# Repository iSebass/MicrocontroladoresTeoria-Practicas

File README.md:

# MicrocontroladoresTeoria-Practicas
Este repositorio ha sido creado como un recurso de apoyo para el curso de Microcontroladores impartido en la Universidad del Valle. En este espacio colaboraremos con el Dr. en Ingeniería Sergio Arenas y el Ing. Juan Sebastián Correa. Nuestro objetivo es desarrollar contenido actualizado que promueva un aprendizaje de los estudiantes.

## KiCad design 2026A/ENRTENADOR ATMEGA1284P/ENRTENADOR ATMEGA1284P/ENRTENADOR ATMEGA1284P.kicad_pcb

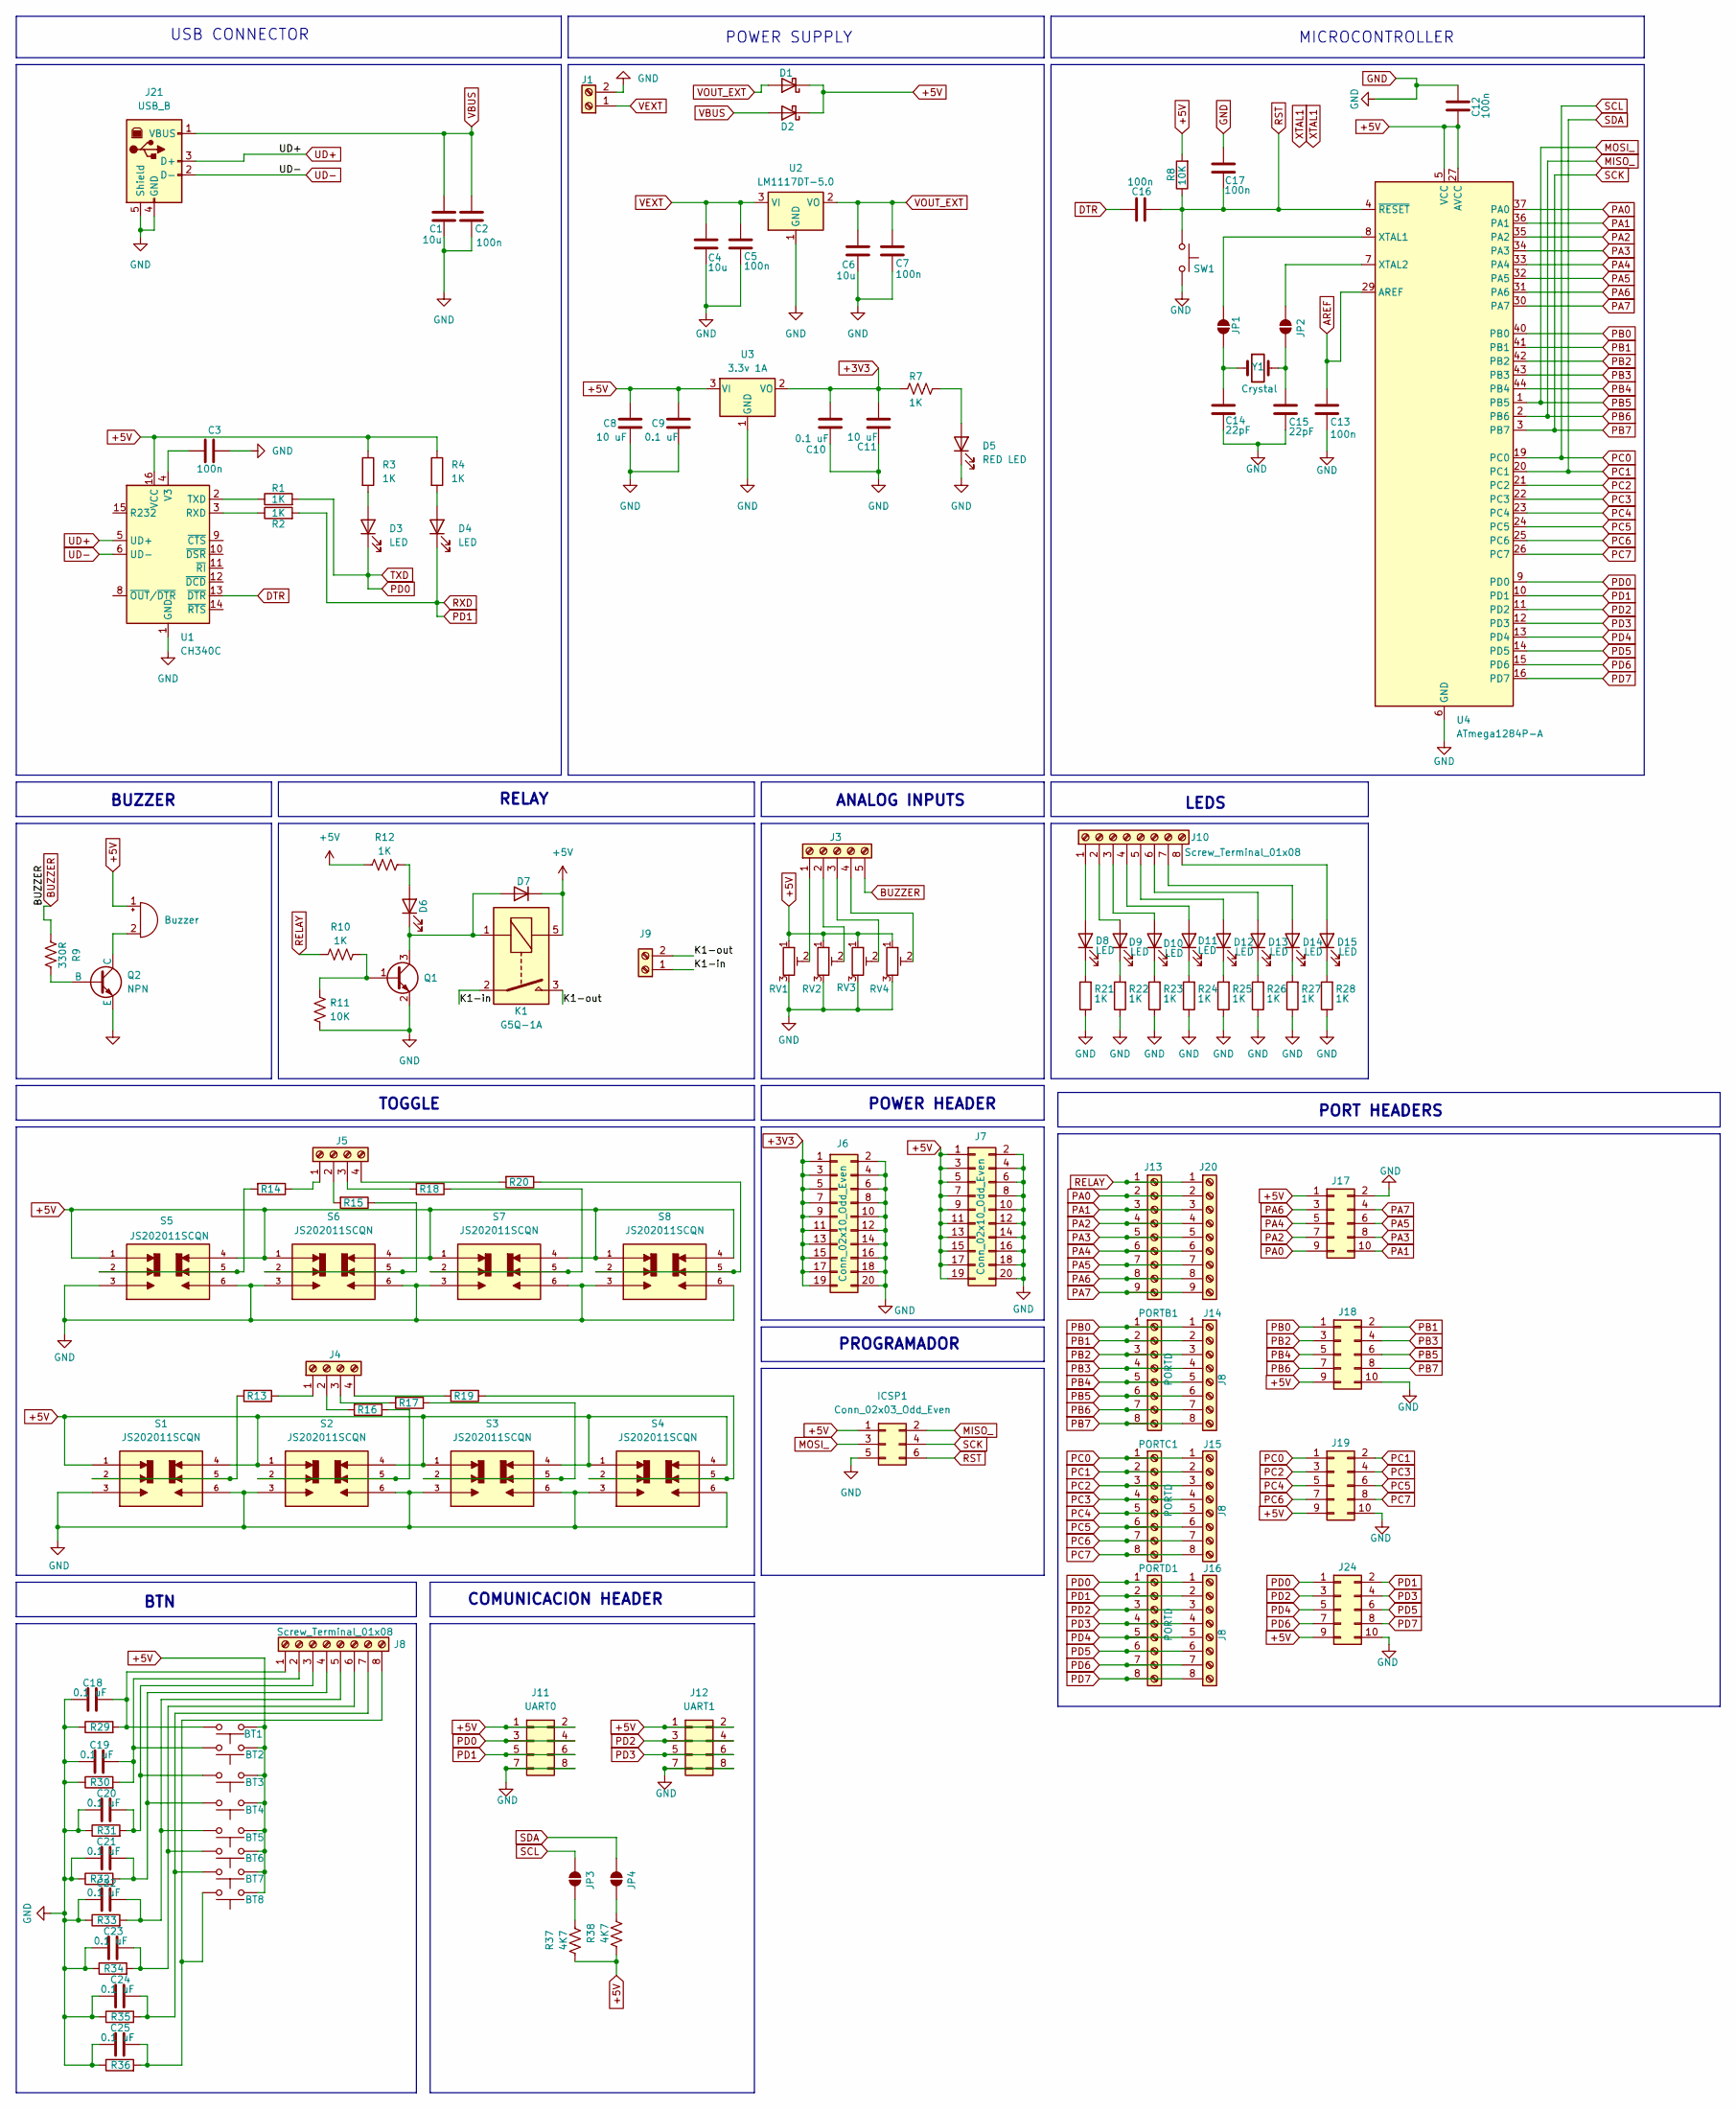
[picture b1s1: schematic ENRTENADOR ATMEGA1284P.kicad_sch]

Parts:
BT1, BT2, BT3, BT4, BT5, BT6, BT7, BT8: SW_Push; SW_SPST_CK_RS282G05A3
BZ1: Buzzer; Buzzer_12x9.5RM7.6
C1, C4, C6: 10u; C_0805_2012Metric
C2, C3, C5, C7, C12, C13, C16, C17: 100n; C_0805_2012Metric
C8, C11: 10 uF; C_0805_2012Metric
C9, C10, C18, C19, C20, C21, C22, C23, C24, C25: 0.1 uF; C_0805_2012Metric
C14, C15: 22pF; C_0805_2012Metric
D1, D2: D_Schottky; D_SMA
D3, D4, D8, D9, D10, D11, D12, D13, D14, D15: LED; LED_0805_2012Metric
D5: RED LED; LED_0805_2012Metric
D6: Green LED; LED_0805_2012Metric
D7: NRVA4007T3G; D_SMA
ICSP1: Conn_02x03_Odd_Even; PinHeader_2x03_P2.54mm_Horizontal
J1, J9: Screw_Terminal_01x02; TerminalBlock_Phoenix_MKDS-1,5-2_1x02_P5.00mm_Horizontal
J3: Screw_Terminal_01x05; PinHeader_1x05_P2.54mm_Vertical
J4, J5: Screw_Terminal_01x04; PinHeader_1x04_P2.54mm_Vertical
J6, J7: Conn_02x10_Odd_Even; PinHeader_2x10_P2.54mm_Vertical
J8, J10: Screw_Terminal_01x08; PinHeader_1x08_P2.54mm_Vertical
J11: UART0; PinHeader_2x04_P2.54mm_Vertical
J12: UART1; PinHeader_2x04_P2.54mm_Vertical
J13, J20: Screw_Terminal_01x09; PinHeader_1x09_P2.54mm_Vertical
J14, J15, J16: J8; PinHeader_1x08_P2.54mm_Vertical
J17, J18, J19, J24: Conn_02x05_Odd_Even; IDC-Header_2x05_P2.54mm_Vertical
J21: USB_B; USB_B_OST_USB-B1HSxx_Horizontal
JP1, JP2, JP3, JP4: SolderJumper_2_Open; SolderJumper-2_P1.3mm_Open_RoundedPad1.0x1.5mm
K1: G5Q-1A; Relay_SPST_Omron-G5Q-1A
PORTB1: PORTD; PinHeader_1x08_P2.54mm_Vertical
PORTC1: PORTD; PinHeader_1x08_P2.54mm_Vertical
PORTD1: PORTD; PinHeader_1x08_P2.54mm_Vertical
Q1: Q_NPN_BEC; SOT-23-3
Q2: NPN; TO-92
R1, R2, R3, R4, R7, R10, R12, R21, R22, R23, R24, R25, R26, R27, R28: 1K; R_0805_2012Metric
R8, R11, R13, R14, R15, R16, R17, R18, R19, R20, R29, R30, R31, R32, R33, R34, R35, R36: 10K; R_0805_2012Metric
R9: 330R; R_1206_3216Metric
R37, R38: 4K7; R_1206_3216Metric
RV1, RV2, RV3, RV4: R_Potentiometer_Trim; Potentiometer_Bourns_TC33X_Vertical
S1, S2, S3, S4, S5, S6, S7, S8: JS202011SCQN; SW_JS202011SCQN; PARTREV 26 May 22
SW1: SW_Push; SW_SPST_CK_RS282G05A3
U1: CH340C; SOIC-16_3.9x9.9mm_P1.27mm
U2: LM1117DT-5.0; TO-252-3_TabPin2
U3: 3.3v 1A; SOT-223-3_TabPin2
U4: ATmega1284P-A; TQFP-44_10x10mm_P0.8mm
Y1: Crystal; Crystal_SMD_HC49-SD

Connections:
+3V3: C10.1, C11.1, J6.1, J6.3, J6.5, J6.7, J6.9, J6.11, J6.13, J6.15, J6.17, J6.19, R7.1, U3.2 (VO)
+5V: BT1.1, BT2.1, BT3.1, BT4.1, BT5.1, BT6.1, BT7.1, BT8.1, BZ1.1 (-), C8.1, C9.1, C12.1, D1.1 (K), D2.1 (K), D7.1 (K), ICSP1.1, J7.1, J7.3, J7.5, J7.7, J7.9, J7.11, J7.13, J7.15, J7.17, J7.19, J11.1, J11.2, J12.1, J12.2, J17.1, J18.9, J19.9, J24.9, K1.5, R3.1, R4.1, R8.2, R12.1, R37.1, R38.1, RV1.1, RV2.1, RV3.1, RV4.1, S1.1, S1.4, S2.1, S2.4, S3.1, S3.4, S4.1, S4.4, S5.1, S5.4, S6.1, S6.4, S7.1, S7.4, S8.1, S8.4, U1.16 (VCC), U3.3 (VI), U4.5 (VCC), U4.17 (VCC), U4.27 (AVCC), U4.38 (VCC)
/K1-in: J9.1, K1.2
/K1-out: J9.2, K1.3
AREF: C13.1, U4.29 (AREF)
BUZZER: J3.5, R9.1
DTR: C16.2, U1.13 (~DTR)
GND: C1.2, C2.2, C3.2, C4.2, C5.2, C6.2, C7.2, C8.2, C9.2, C10.2, C11.2, C12.2, C13.2, C14.2, C15.2, C17.2, C18.1, C19.1, C20.1, C21.1, C22.1, C23.1, C24.1, C25.1, D5.1 (K), ICSP1.5, J1.2, J6.2, J6.4, J6.6, J6.8, J6.10, J6.12, J6.14, J6.16, J6.18, J6.20, J7.2, J7.4, J7.6, J7.8, J7.10, J7.12, J7.14, J7.16, J7.18, J7.20, J11.7, J11.8, J12.7, J12.8, J17.2, J18.10, J19.10, J21.4 (GND), J21.5 (Shield), J24.10, Q1.2 (E), Q2.3 (E), R11.1, R21.1, R22.1, R23.1, R24.1, R25.1, R26.1, R27.1, R28.1, R29.1, R30.1, R31.1, R32.1, R33.1, R34.1, R35.1, R36.1, RV1.3, RV2.3, RV3.3, RV4.3, S1.3, S1.6, S2.3, S2.6, S3.3, S3.6, S4.3, S4.6, S5.3, S5.6, S6.3, S6.6, S7.3, S7.6, S8.3, S8.6, SW1.2, U1.1 (GND), U2.1 (GND), U3.1 (GND), U4.6 (GND), U4.18 (GND), U4.28 (GND), U4.39 (GND)
MISO_: ICSP1.2, J14.7, J18.7, PORTB1.7, U4.2 (PB6)
MOSI_: ICSP1.3, J14.6, J18.6, PORTB1.6, U4.1 (PB5)
unnamed: BZ1.2 (+), Q2.1 (C)
unnamed: D3.2 (A), R3.2
unnamed: D4.2 (A), R4.2
unnamed: D5.2 (A), R7.2
unnamed: D6.2 (A), R12.2
unnamed: D6.1 (K), D7.2 (A), K1.1, Q1.3 (C)
unnamed: D8.2 (A), J10.1
unnamed: D8.1 (K), R21.2
unnamed: D9.2 (A), J10.2
unnamed: D9.1 (K), R22.2
unnamed: D10.2 (A), J10.3
unnamed: D10.1 (K), R23.2
unnamed: D11.2 (A), J10.4
unnamed: D11.1 (K), R24.2
unnamed: D12.2 (A), J10.5
unnamed: D12.1 (K), R25.2
unnamed: D13.2 (A), J10.6
unnamed: D13.1 (K), R26.2
unnamed: D14.2 (A), J10.7
unnamed: D14.1 (K), R27.2
unnamed: D15.2 (A), J10.8
unnamed: D15.1 (K), R28.2
unnamed: J3.1, RV1.2
unnamed: J3.2, RV2.2
unnamed: J3.3, RV3.2
unnamed: J3.4, RV4.2
unnamed: J4.1, R13.1
unnamed: J4.2, R16.2
unnamed: J4.3, R17.2
unnamed: J4.4, R19.2
unnamed: J5.1, R14.1
unnamed: J5.2, R15.2
unnamed: J5.3, R18.2
unnamed: J5.4, R20.2
unnamed: BT1.2, C18.2, J8.1, R29.2
unnamed: BT2.2, C19.2, J8.2, R30.2
unnamed: BT3.2, C20.2, J8.3, R31.2
unnamed: BT4.2, C21.2, J8.4, R32.2
unnamed: BT5.2, C22.2, J8.5, R33.2
unnamed: BT6.2, C23.2, J8.6, R34.2
unnamed: BT7.2, C24.2, J8.7, R35.2
unnamed: BT8.2, C25.2, J8.8, R36.2
unnamed: JP1.1 (A), U4.8 (XTAL1)
unnamed: C14.1, JP1.2 (B), Y1.1
unnamed: JP2.1 (A), U4.7 (XTAL2)
unnamed: C15.1, JP2.2 (B), Y1.2
unnamed: JP3.2 (B), R37.2
unnamed: JP4.2 (B), R38.2
unnamed: Q1.1 (B), R10.2, R11.2
unnamed: Q2.2 (B), R9.2
unnamed: R13.2, S1.2, S1.5
unnamed: R14.2, S5.2, S5.5
unnamed: R15.1, S6.2, S6.5
unnamed: R16.1, S2.2, S2.5
unnamed: R17.1, S3.2, S3.5
unnamed: R18.1, S7.2, S7.5
unnamed: R19.1, S4.2, S4.5
unnamed: R20.1, S8.2, S8.5
unnamed: R2.1, U1.3 (RXD)
unnamed: R1.1, U1.2 (TXD)
unnamed: C3.1, U1.4 (V3)
PA0: J13.2, J17.9, J20.2, U4.37 (PA0)
PA1: J13.3, J17.10, J20.3, U4.36 (PA1)
PA2: J13.4, J17.7, J20.4, U4.35 (PA2)
PA3: J13.5, J17.8, J20.5, U4.34 (PA3)
PA4: J13.6, J17.5, J20.6, U4.33 (PA4)
PA5: J13.7, J17.6, J20.7, U4.32 (PA5)
PA6: J13.8, J17.3, J20.8, U4.31 (PA6)
PA7: J13.9, J17.4, J20.9, U4.30 (PA7)
PB0: J14.1, J18.1, PORTB1.1, U4.40 (PB0)
PB1: J14.2, J18.2, PORTB1.2, U4.41 (PB1)
PB2: J14.3, J18.3, PORTB1.3, U4.42 (PB2)
PB3: J14.4, J18.4, PORTB1.4, U4.43 (PB3)
PB4: J14.5, J18.5, PORTB1.5, U4.44 (PB4)
PB7: ICSP1.4, J14.8, J18.8, PORTB1.8, U4.3 (PB7)
PC0: J15.1, J19.1, JP3.1 (A), PORTC1.1, U4.19 (PC0)
PC1: J15.2, J19.2, JP4.1 (A), PORTC1.2, U4.20 (PC1)
PC2: J15.3, J19.3, PORTC1.3, U4.21 (PC2)
PC3: J15.4, J19.4, PORTC1.4, U4.22 (PC3)
PC4: J15.5, J19.5, PORTC1.5, U4.23 (PC4)
PC5: J15.6, J19.6, PORTC1.6, U4.24 (PC5)
PC6: J15.7, J19.7, PORTC1.7, U4.25 (PC6)
PC7: J15.8, J19.8, PORTC1.8, U4.26 (PC7)
PD0: D3.1 (K), J11.3, J11.4, J16.1, J24.1, PORTD1.1, R1.2, U4.9 (PD0)
PD1: D4.1 (K), J11.5, J11.6, J16.2, J24.2, PORTD1.2, R2.2, U4.10 (PD1)
PD2: J12.3, J12.4, J16.3, J24.3, PORTD1.3, U4.11 (PD2)
PD3: J12.5, J12.6, J16.4, J24.4, PORTD1.4, U4.12 (PD3)
PD4: J16.5, J24.5, PORTD1.5, U4.13 (PD4)
PD5: J16.6, J24.6, PORTD1.6, U4.14 (PD5)
PD6: J16.7, J24.7, PORTD1.7, U4.15 (PD6)
PD7: J16.8, J24.8, PORTD1.8, U4.16 (PD7)
RELAY: J13.1, J20.1, R10.1
RST: C16.1, C17.1, ICSP1.6, R8.1, SW1.1, U4.4 (~RESET)
UD+: J21.3 (D+), U1.5 (UD+)
UD-: J21.2 (D-), U1.6 (UD-)
VBUS: C1.1, C2.1, D2.2 (A), J21.1 (VBUS)
VEXT: C4.1, C5.1, J1.1, U2.3 (VI)
VOUT_EXT: C6.1, C7.1, D1.2 (A), U2.2 (VO)

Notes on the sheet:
LEDS
PROGRAMADOR
COMUNICACION HEADER
POWER SUPPLY
BUZZER
ANALOG INPUTS
TOGGLE
BTN
RELAY
PORT HEADERS
MICROCONTROLLER
POWER HEADER
USB CONNECTOR

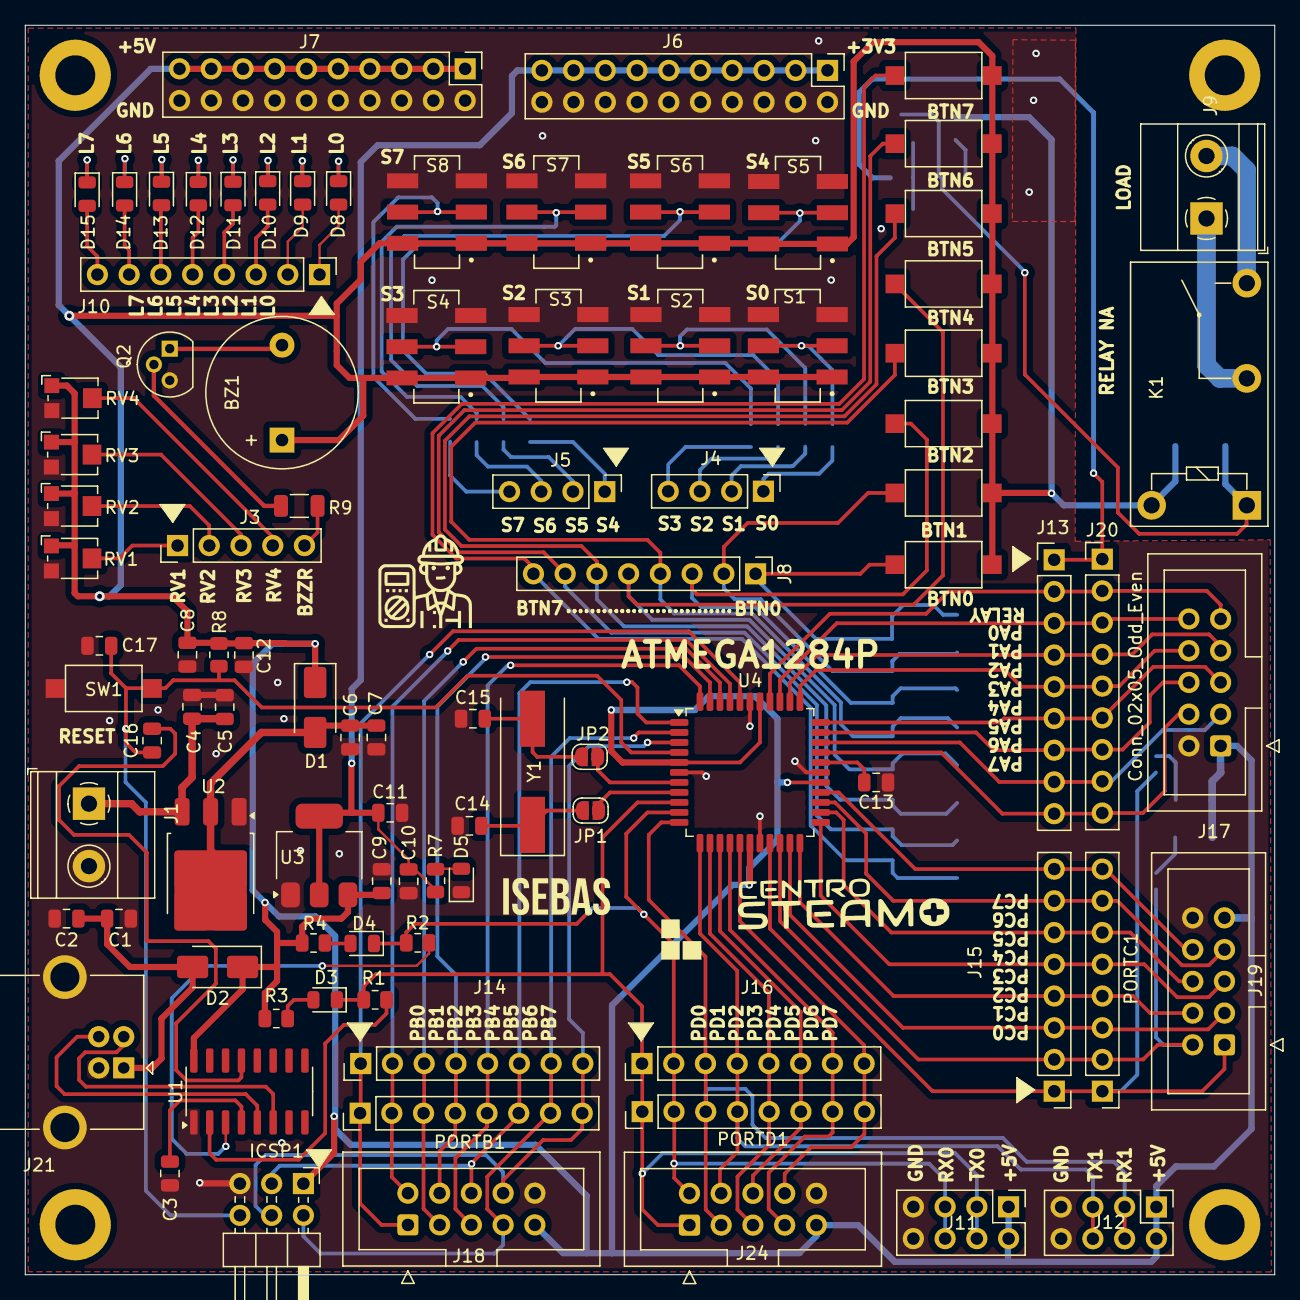
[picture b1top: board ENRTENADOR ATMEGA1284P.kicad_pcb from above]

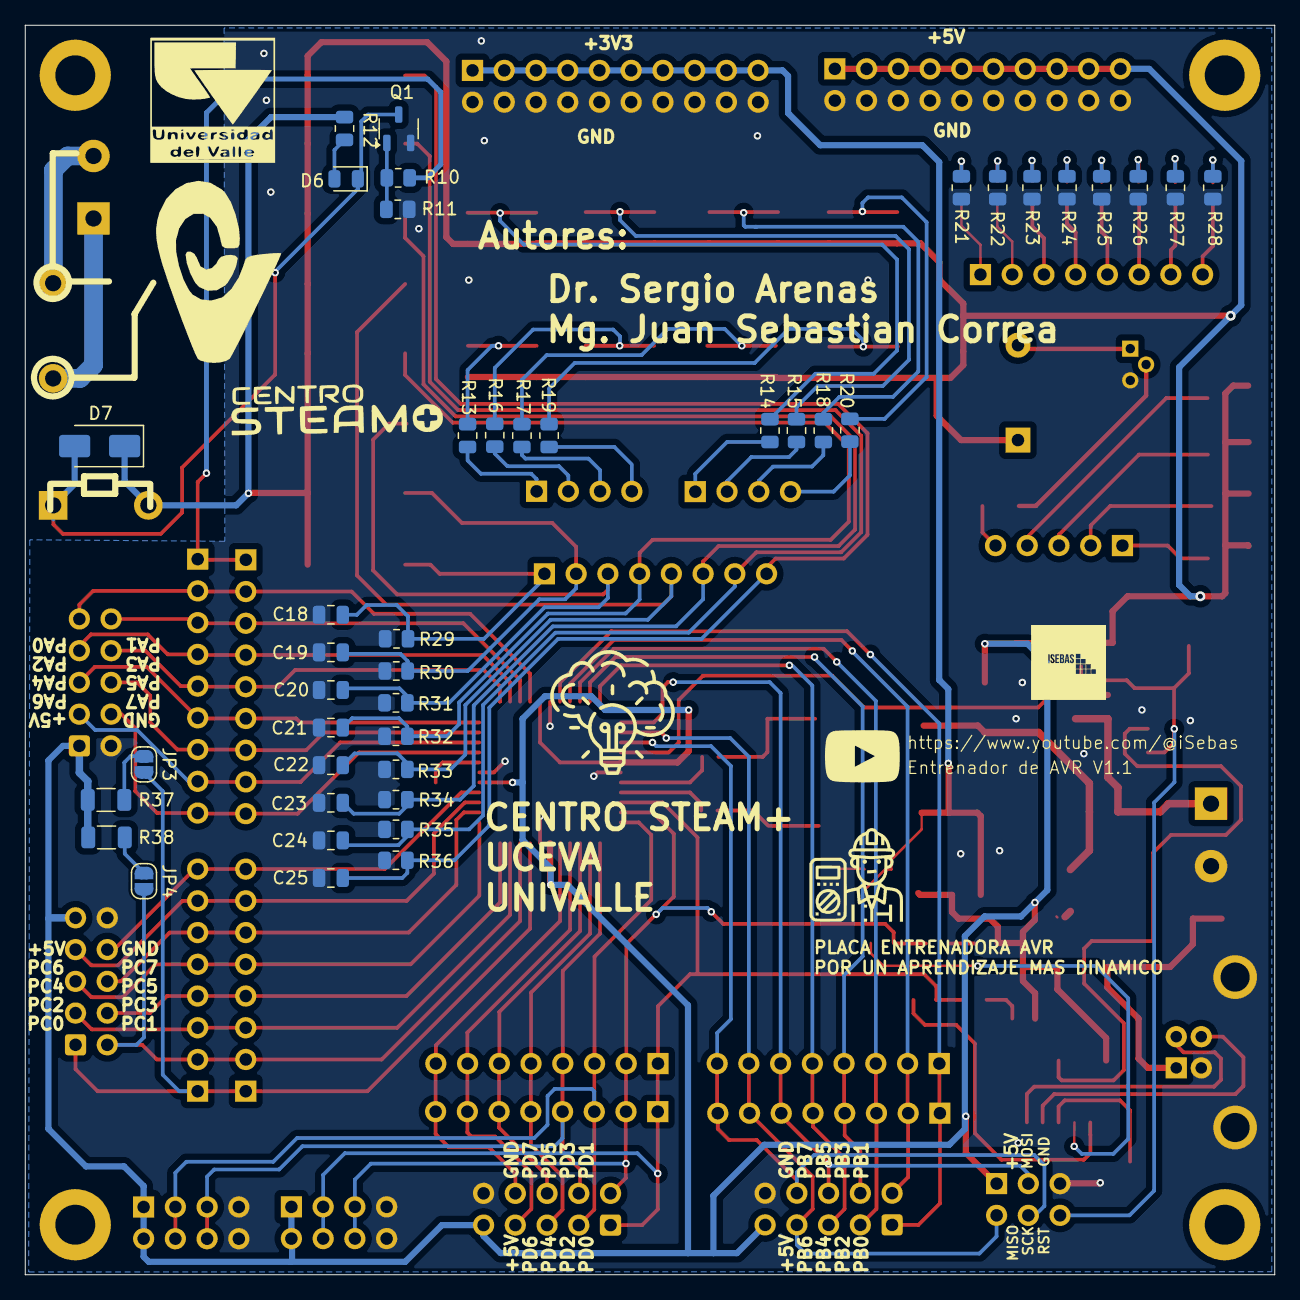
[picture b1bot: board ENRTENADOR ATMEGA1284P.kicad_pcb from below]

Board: 2 copper layers, 100.0 x 100.0 mm, 135 parts (42 on the bottom side), 108 nets.

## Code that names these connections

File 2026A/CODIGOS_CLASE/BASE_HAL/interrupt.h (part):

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       especificos pueden disparar la IRQ.
       PCMSK0 -> banco 0, PCMSK1 -> banco 1, etc.

   Ejemplo tipico: habilitar PCINT en PB3 (banco 0, pin 3)
     HAL_PCINT_PIN_ENABLE(PCMSK0, (1 << PCINT3));
     HAL_PCINT_BANK_ENABLE(HAL_PCINT_BANK0);
   ========================================= */
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 * -----------------------------------------------------------
 * EJEMPLO 1: Boton en INT0 con flanco de bajada
 * -----------------------------------------------------------
 * Esquema: boton conectado entre PD2 (INT0) y GND,
 *          pull-up interno activado.
 * Cuando el boton se presiona: PD2 pasa de 5V a 0V (bajada).
 *
 * #include "interrupt.h"
 * #include "gpio.h"
 *
 * static void on_boton(void) {
 *     GPIO_TOGGLE_PORTB(5);   // togglear LED en PB5
 * }
 *
 * int main(void) {
 *     GPIO_PIN_MODE_PORTB(5, OUTPUT);
 *     GPIO_PIN_MODE_PORTD(2, INPUT);
 *     GPIO_PULLUP_PORTD(2, HIGH);             // activar pull-up en PD2
 *
 *     HAL_EXT_INT_RegisterCallback(HAL_EXT_INT0, HAL_IRQ_SENSE_FALL, on_boton);
 *     HAL_EXT_INT_CLEAR_FLAG(HAL_EXT_INT0);   // descartar flancos previos
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 * }
 * -----------------------------------------------------------
 *
 * EJEMPLO 2: Encoder rotativo en PCINT (banco 0, pines PB0 y PB1)
 * -----------------------------------------------------------
 * Las PCINT son ideales para encoders porque necesitas detectar
 * cambios en dos pines distintos con un solo vector.
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 * #include "interrupt.h"
 *
 * static void on_encoder(void) {
 *     uint8_t estado = GPIO_PORT_READ(PINB) & 0x03U;  // leer PB0 y PB1
 *     // logica de decodificacion del encoder aqui
 * }
 *
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
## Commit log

2024-12-03 Se agregan carpetas para distribuir de forma ordenada los recursos del curso.
2025-01-03 Se agregan planos de entrenador en KiCad
2025-03-07 Se agrega codigo de secuencia de luces forzada
2025-03-07 Se agrega codigos de clase de entradas y salidas digitales
2025-03-14 Se agregan libreriaas y material de clase 13 de marzo
2025-03-24 Entrenador 2025A MARZO 24
2025-04-25 Se agregan codigos de clase UART
2025-05-09 Se agrega librerias
2025-09-03 Se organiza carpeta y se agrega entrenador con modificaciones y listados de componentes actualizados
2025-09-03 Se organiza el repositorio por años
2025-09-03 Se agregan los codigos de la segunda clase
2025-09-04 Se agregan codigos de clase
2025-09-04 Se actualiza listados
2025-09-04 Se actualiza listado
2025-09-13 Se agregan codigos de la clase 10 de Septiembre
2025-09-18 Se agregan codigos de la libreria LCD
2025-09-20 Se agregan codigos de clase LCD
2025-10-30 SE agrega codigo de consulta JORE
2026-02-26 Se agrega codigo de clase semana 03 - GPIO - Salidas digitales y configuracion global
2026-03-05 Se agregan proyecto con archivo de configuracion del cutso Config.h
2026-03-05 Se agrega libreria de 7 segmentos
2026-03-11 Se agrega codigo de la HAL de base
2026-03-11 Se agrega entrenador
2026-03-12 Se agrega codigo de multiplexacion de display
2026-03-18 Se agregan archivos de la HAL completa a usar en el curso de SISTEMAS EMBEBIDOS
2026-03-18 Create README.md for AVR-HAL
    Added README.md for AVR-HAL project with detailed documentation.
2026-03-18 Update print statement from 'Hello' to 'Goodbye'
2026-04-16 Se agregan codigos de clase ADC y LCD
